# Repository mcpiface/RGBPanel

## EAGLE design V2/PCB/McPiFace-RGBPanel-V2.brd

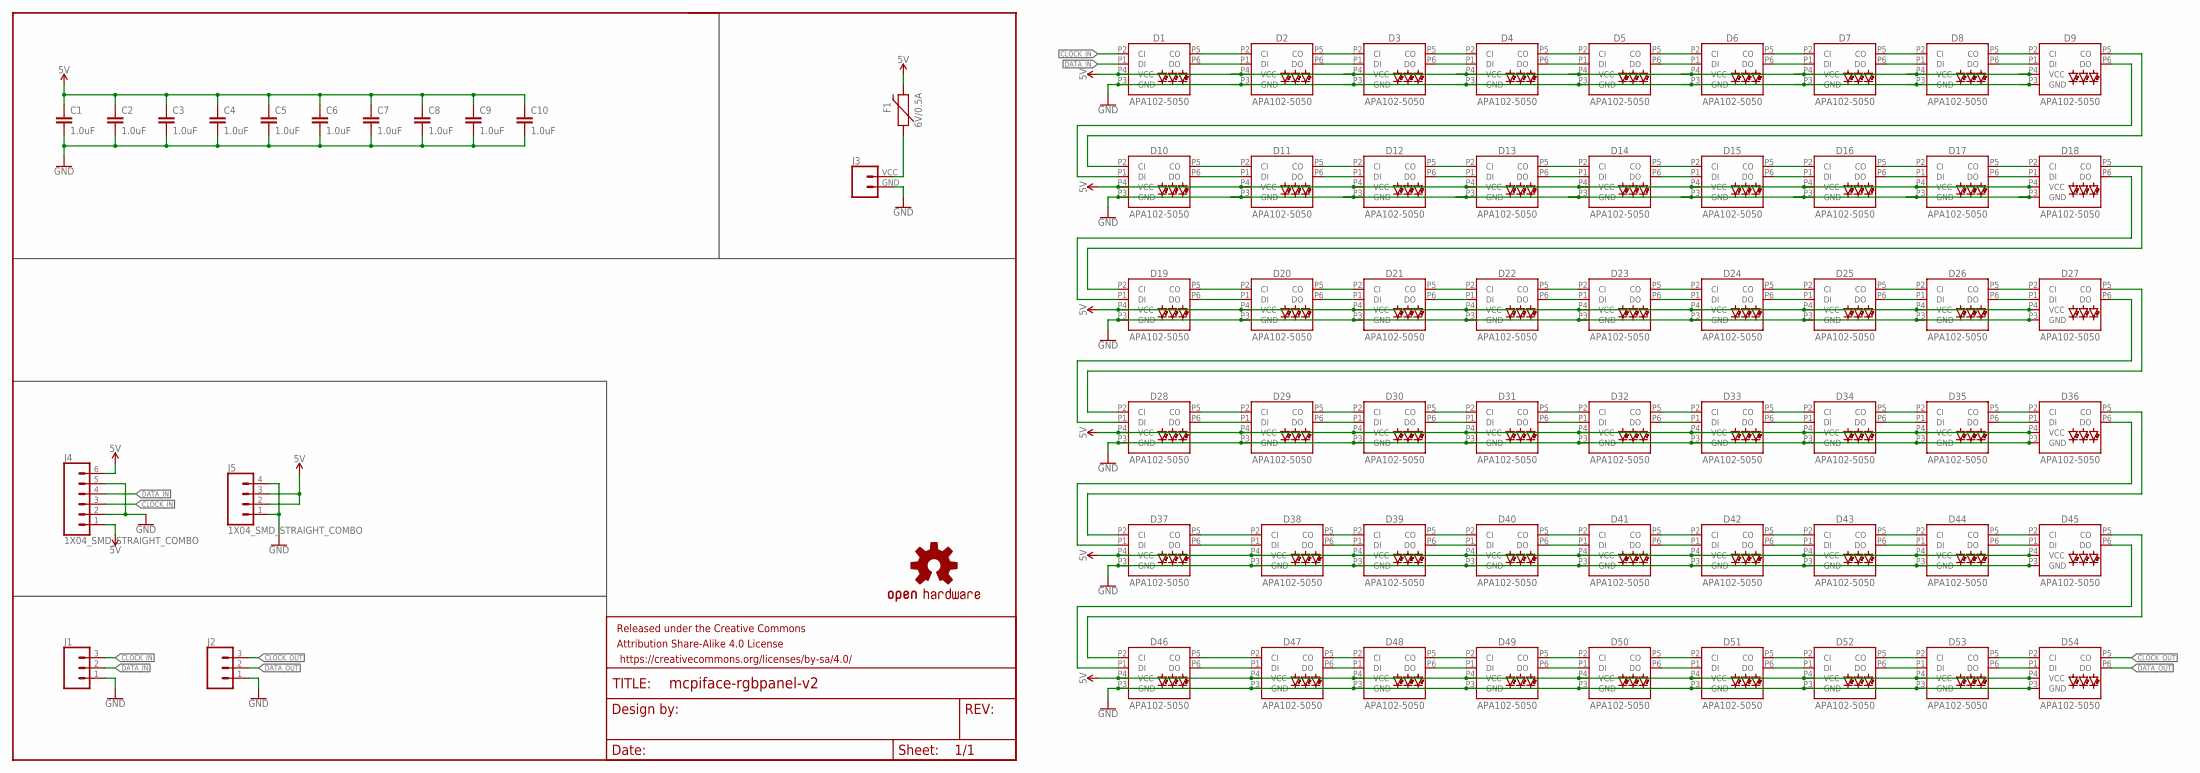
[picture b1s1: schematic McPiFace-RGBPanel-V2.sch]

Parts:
C1, C2, C3, C4, C5, C6, C7, C8, C9, C10: 1.0uF; 0805-CAP
D1, D2, D3, D4, D5, D6, D7, D8, D9, D10, D11, D12, D13, D14, D15, D16, D17, D18, D19, D20, D21, D22, D23, D24, D25, D26, D27, D28, D29, D30, D31, D32, D33, D34, D35, D36, D37, D38, D39, D40, D41, D42, D43, D44, D45, D46, D47, D48, D49, D50, D51, D52, D53, D54: APA102-5050
F1: 6V/0.5A; 1206
FRAME1: FRAME-LETTER; CREATIVE_COMMONS
J1, J2: CONN_03SMD; 1X03-1MM-RA
J3: CONN_02JST-2-PH-VERT; JST-2-SMD-VERT
J4: 1X04_SMD_STRAIGHT_COMBO; 1X06_SMD_STRAIGHT_COMBO
J5: 1X04_SMD_STRAIGHT_COMBO; 1X04_SMD_VERTICAL_COMBO
LOGO1: OSHW-LOGOL; OSHW-LOGO-L

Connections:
5V: C1.1, C2.1, C3.1, C4.1, C5.1, C6.1, C7.1, C8.1, C9.1, C10.1, D1.P4 (VCC), D2.P4 (VCC), D3.P4 (VCC), D4.P4 (VCC), D5.P4 (VCC), D6.P4 (VCC), D7.P4 (VCC), D8.P4 (VCC), D9.P4 (VCC), D10.P4 (VCC), D11.P4 (VCC), D12.P4 (VCC), D13.P4 (VCC), D14.P4 (VCC), D15.P4 (VCC), D16.P4 (VCC), D17.P4 (VCC), D18.P4 (VCC), D19.P4 (VCC), D20.P4 (VCC), D21.P4 (VCC), D22.P4 (VCC), D23.P4 (VCC), D24.P4 (VCC), D25.P4 (VCC), D26.P4 (VCC), D27.P4 (VCC), D28.P4 (VCC), D29.P4 (VCC), D30.P4 (VCC), D31.P4 (VCC), D32.P4 (VCC), D33.P4 (VCC), D34.P4 (VCC), D35.P4 (VCC), D36.P4 (VCC), D37.P4 (VCC), D38.P4 (VCC), D39.P4 (VCC), D40.P4 (VCC), D41.P4 (VCC), D42.P4 (VCC), D43.P4 (VCC), D44.P4 (VCC), D45.P4 (VCC), D46.P4 (VCC), D47.P4 (VCC), D48.P4 (VCC), D49.P4 (VCC), D50.P4 (VCC), D51.P4 (VCC), D52.P4 (VCC), D53.P4 (VCC), D54.P4 (VCC), F1.2, J4.1, J4.6, J5.2, J5.3
CLOCK_IN: D1.P2 (CI), J1.3, J4.3
CLOCK_OUT: D54.P5 (CO), J2.3
DATA_IN: D1.P1 (DI), J1.2, J4.4
DATA_OUT: D54.P6 (DO), J2.2
GND: C1.2, C2.2, C3.2, C4.2, C5.2, C6.2, C7.2, C8.2, C9.2, C10.2, D1.P3 (GND), D2.P3 (GND), D3.P3 (GND), D4.P3 (GND), D5.P3 (GND), D6.P3 (GND), D7.P3 (GND), D8.P3 (GND), D9.P3 (GND), D10.P3 (GND), D11.P3 (GND), D12.P3 (GND), D13.P3 (GND), D14.P3 (GND), D15.P3 (GND), D16.P3 (GND), D17.P3 (GND), D18.P3 (GND), D19.P3 (GND), D20.P3 (GND), D21.P3 (GND), D22.P3 (GND), D23.P3 (GND), D24.P3 (GND), D25.P3 (GND), D26.P3 (GND), D27.P3 (GND), D28.P3 (GND), D29.P3 (GND), D30.P3 (GND), D31.P3 (GND), D32.P3 (GND), D33.P3 (GND), D34.P3 (GND), D35.P3 (GND), D36.P3 (GND), D37.P3 (GND), D38.P3 (GND), D39.P3 (GND), D40.P3 (GND), D41.P3 (GND), D42.P3 (GND), D43.P3 (GND), D44.P3 (GND), D45.P3 (GND), D46.P3 (GND), D47.P3 (GND), D48.P3 (GND), D49.P3 (GND), D50.P3 (GND), D51.P3 (GND), D52.P3 (GND), D53.P3 (GND), D54.P3 (GND), J1.1, J2.1, J3.GND (1), J4.2, J4.5, J5.1, J5.4
unnamed: D10.P5 (CO), D11.P2 (CI)
unnamed: D10.P6 (DO), D11.P1 (DI)
unnamed: D11.P5 (CO), D12.P2 (CI)
unnamed: D11.P6 (DO), D12.P1 (DI)
unnamed: F1.1, J3.VCC (2)
unnamed: D9.P5 (CO), D10.P2 (CI)
unnamed: D9.P6 (DO), D10.P1 (DI)
unnamed: D18.P6 (DO), D19.P1 (DI)
unnamed: D18.P5 (CO), D19.P2 (CI)
unnamed: D15.P5 (CO), D16.P2 (CI)
unnamed: D15.P6 (DO), D16.P1 (DI)
unnamed: D12.P5 (CO), D13.P2 (CI)
unnamed: D12.P6 (DO), D13.P1 (DI)
unnamed: D19.P6 (DO), D20.P1 (DI)
unnamed: D16.P5 (CO), D17.P2 (CI)
unnamed: D19.P5 (CO), D20.P2 (CI)
unnamed: D16.P6 (DO), D17.P1 (DI)
unnamed: D13.P5 (CO), D14.P2 (CI)
unnamed: D13.P6 (DO), D14.P1 (DI)
unnamed: D14.P6 (DO), D15.P1 (DI)
unnamed: D14.P5 (CO), D15.P2 (CI)
unnamed: D20.P6 (DO), D21.P1 (DI)
unnamed: D1.P5 (CO), D2.P2 (CI)
unnamed: D17.P5 (CO), D18.P2 (CI)
unnamed: D17.P6 (DO), D18.P1 (DI)
unnamed: D20.P5 (CO), D21.P2 (CI)
unnamed: D21.P6 (DO), D22.P1 (DI)
unnamed: D21.P5 (CO), D22.P2 (CI)
unnamed: D22.P6 (DO), D23.P1 (DI)
unnamed: D22.P5 (CO), D23.P2 (CI)
unnamed: D23.P6 (DO), D24.P1 (DI)
unnamed: D23.P5 (CO), D24.P2 (CI)
unnamed: D24.P6 (DO), D25.P1 (DI)
unnamed: D24.P5 (CO), D25.P2 (CI)
unnamed: D25.P6 (DO), D26.P1 (DI)
unnamed: D1.P6 (DO), D2.P1 (DI)
unnamed: D25.P5 (CO), D26.P2 (CI)
unnamed: D26.P6 (DO), D27.P1 (DI)
unnamed: D26.P5 (CO), D27.P2 (CI)
unnamed: D27.P5 (CO), D28.P2 (CI)
unnamed: D27.P6 (DO), D28.P1 (DI)
unnamed: D28.P6 (DO), D29.P1 (DI)
unnamed: D28.P5 (CO), D29.P2 (CI)
unnamed: D29.P6 (DO), D30.P1 (DI)
unnamed: D29.P5 (CO), D30.P2 (CI)
unnamed: D30.P6 (DO), D31.P1 (DI)
unnamed: D30.P5 (CO), D31.P2 (CI)
unnamed: D31.P6 (DO), D32.P1 (DI)
unnamed: D31.P5 (CO), D32.P2 (CI)
unnamed: D32.P6 (DO), D33.P1 (DI)
unnamed: D32.P5 (CO), D33.P2 (CI)
unnamed: D33.P6 (DO), D34.P1 (DI)
unnamed: D33.P5 (CO), D34.P2 (CI)
unnamed: D34.P6 (DO), D35.P1 (DI)
unnamed: D34.P5 (CO), D35.P2 (CI)
unnamed: D35.P6 (DO), D36.P1 (DI)
unnamed: D35.P5 (CO), D36.P2 (CI)
unnamed: D36.P5 (CO), D37.P2 (CI)
unnamed: D36.P6 (DO), D37.P1 (DI)
unnamed: D37.P6 (DO), D38.P1 (DI)
unnamed: D37.P5 (CO), D38.P2 (CI)
unnamed: D38.P6 (DO), D39.P1 (DI)
unnamed: D38.P5 (CO), D39.P2 (CI)
unnamed: D39.P6 (DO), D40.P1 (DI)
unnamed: D39.P5 (CO), D40.P2 (CI)
unnamed: D40.P6 (DO), D41.P1 (DI)
unnamed: D40.P5 (CO), D41.P2 (CI)
unnamed: D2.P5 (CO), D3.P2 (CI)
unnamed: D2.P6 (DO), D3.P1 (DI)
unnamed: D3.P5 (CO), D4.P2 (CI)
unnamed: D3.P6 (DO), D4.P1 (DI)
unnamed: D4.P5 (CO), D5.P2 (CI)
unnamed: D4.P6 (DO), D5.P1 (DI)
unnamed: D5.P5 (CO), D6.P2 (CI)
unnamed: D5.P6 (DO), D6.P1 (DI)
unnamed: D6.P5 (CO), D7.P2 (CI)
unnamed: D6.P6 (DO), D7.P1 (DI)
unnamed: D7.P5 (CO), D8.P2 (CI)
unnamed: D7.P6 (DO), D8.P1 (DI)
unnamed: D8.P5 (CO), D9.P2 (CI)
unnamed: D8.P6 (DO), D9.P1 (DI)
unnamed: D41.P6 (DO), D42.P1 (DI)
unnamed: D41.P5 (CO), D42.P2 (CI)
unnamed: D42.P6 (DO), D43.P1 (DI)
unnamed: D42.P5 (CO), D43.P2 (CI)
unnamed: D43.P6 (DO), D44.P1 (DI)
unnamed: D43.P5 (CO), D44.P2 (CI)
unnamed: D44.P6 (DO), D45.P1 (DI)
unnamed: D44.P5 (CO), D45.P2 (CI)
unnamed: D45.P6 (DO), D46.P1 (DI)
unnamed: D45.P5 (CO), D46.P2 (CI)
unnamed: D46.P6 (DO), D47.P1 (DI)
unnamed: D46.P5 (CO), D47.P2 (CI)
unnamed: D47.P6 (DO), D48.P1 (DI)
unnamed: D47.P5 (CO), D48.P2 (CI)
unnamed: D48.P6 (DO), D49.P1 (DI)
unnamed: D48.P5 (CO), D49.P2 (CI)
unnamed: D49.P6 (DO), D50.P1 (DI)
unnamed: D49.P5 (CO), D50.P2 (CI)
unnamed: D50.P6 (DO), D51.P1 (DI)
unnamed: D50.P5 (CO), D51.P2 (CI)
unnamed: D51.P6 (DO), D52.P1 (DI)
unnamed: D51.P5 (CO), D52.P2 (CI)
unnamed: D52.P6 (DO), D53.P1 (DI)
unnamed: D52.P5 (CO), D53.P2 (CI)
unnamed: D53.P6 (DO), D54.P1 (DI)
unnamed: D53.P5 (CO), D54.P2 (CI)

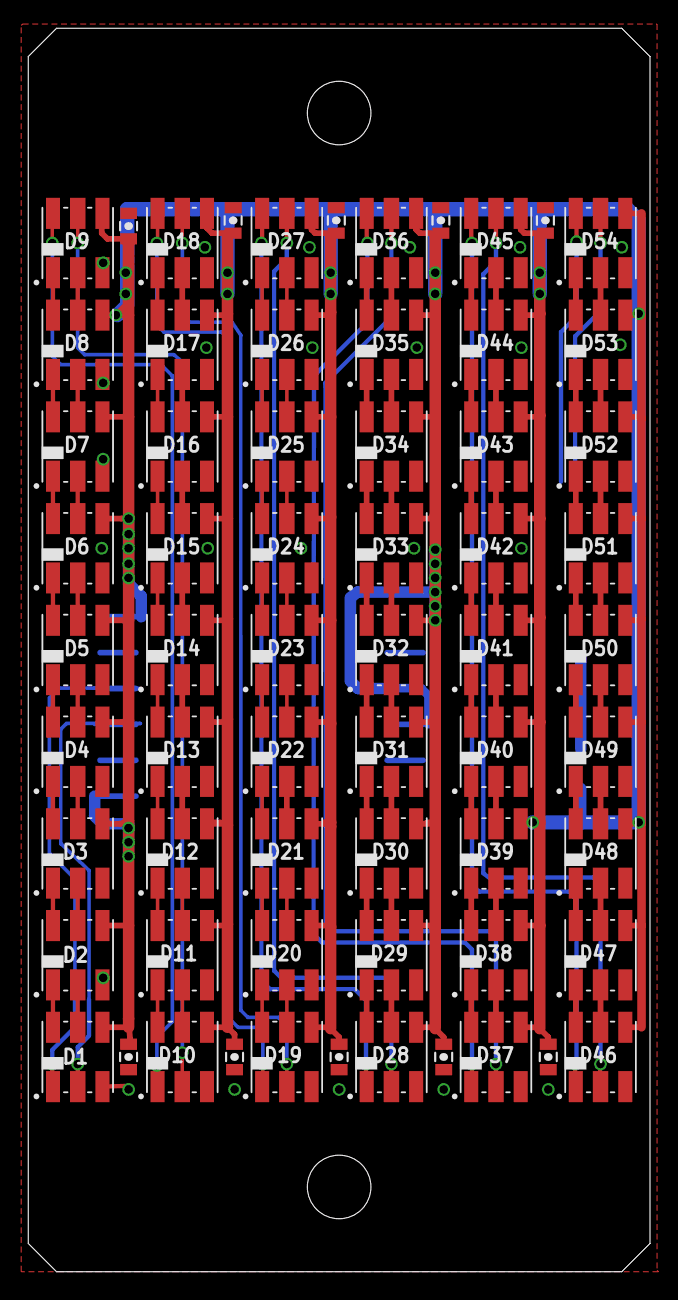
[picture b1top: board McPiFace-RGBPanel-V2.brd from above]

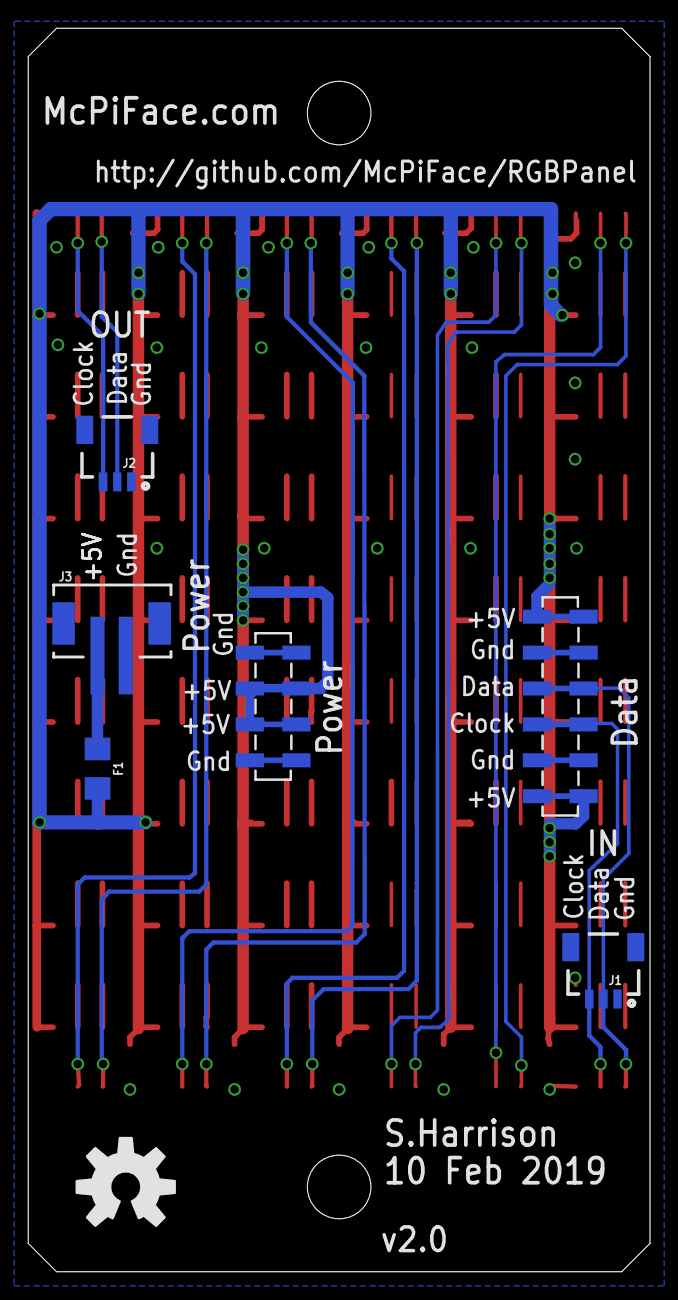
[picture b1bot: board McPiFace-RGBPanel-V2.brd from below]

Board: 2 copper layers, 44.0 x 88.0 mm, 72 parts (7 on the bottom side), 113 nets.

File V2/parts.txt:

Partlist

Exported from McPiFace-RGBPanel-V2.brd at 10/02/2019 03:54

EAGLE Version 7.4.0 Copyright (c) 1988-2015 CadSoft

Assembly variant: 

Part     Value                   Package                 Library             Position (mm)         Orientation

C1       1.0uF                   0805-CAP                SparkFun-Capacitors (29.4 15.2)           R270
C2       1.0uF                   0805-CAP                SparkFun-Capacitors (21.8 74.4)           R90
C3       1.0uF                   0805-CAP                SparkFun-Capacitors (29.2 74.4)           R90
C4       1.0uF                   0805-CAP                SparkFun-Capacitors (14.5 74.4)           R90
C5       1.0uF                   0805-CAP                SparkFun-Capacitors (14.6 15.2)           R270
C6       1.0uF                   0805-CAP                SparkFun-Capacitors (7.1 15.2)            R270
C7       1.0uF                   0805-CAP                SparkFun-Capacitors (22 15.2)             R270
C8       1.0uF                   0805-CAP                SparkFun-Capacitors (36.8 15.2)           R270
C9       1.0uF                   0805-CAP                SparkFun-Capacitors (7.1 74)              R90
C10      1.0uF                   0805-CAP                SparkFun-Capacitors (36.6 74.4)           R90
D1       APA102-5050             APA102-5050             SparkFun-LED        (3.5 15.2)            R0
D2       APA102-5050             APA102-5050             SparkFun-LED        (3.5 22.4)            R0
D3       APA102-5050             APA102-5050             SparkFun-LED        (3.5 29.6)            R0
D4       APA102-5050             APA102-5050             SparkFun-LED        (3.5 36.8)            R0
D5       APA102-5050             APA102-5050             SparkFun-LED        (3.5 44)              R0
D6       APA102-5050             APA102-5050             SparkFun-LED        (3.5 51.2)            R0
D7       APA102-5050             APA102-5050             SparkFun-LED        (3.5 58.4)            R0
D8       APA102-5050             APA102-5050             SparkFun-LED        (3.5 65.6)            R0
D9       APA102-5050             APA102-5050             SparkFun-LED        (3.5 72.8)            R0
D10      APA102-5050             APA102-5050             SparkFun-LED        (10.9 15.2)           R0
D11      APA102-5050             APA102-5050             SparkFun-LED        (10.9 22.4)           R0
D12      APA102-5050             APA102-5050             SparkFun-LED        (10.9 29.6)           R0
D13      APA102-5050             APA102-5050             SparkFun-LED        (10.9 36.8)           R0
D14      APA102-5050             APA102-5050             SparkFun-LED        (10.9 44)             R0
D15      APA102-5050             APA102-5050             SparkFun-LED        (10.9 51.2)           R0
D16      APA102-5050             APA102-5050             SparkFun-LED        (10.9 58.4)           R0
D17      APA102-5050             APA102-5050             SparkFun-LED        (10.9 65.6)           R0
D18      APA102-5050             APA102-5050             SparkFun-LED        (10.9 72.8)           R0
D19      APA102-5050             APA102-5050             SparkFun-LED        (18.3 15.2)           R0
D20      APA102-5050             APA102-5050             SparkFun-LED        (18.3 22.4)           R0
D21      APA102-5050             APA102-5050             SparkFun-LED        (18.3 29.6)           R0
D22      APA102-5050             APA102-5050             SparkFun-LED        (18.3 36.8)           R0
D23      APA102-5050             APA102-5050             SparkFun-LED        (18.3 44)             R0
D24      APA102-5050             APA102-5050             SparkFun-LED        (18.3 51.2)           R0
D25      APA102-5050             APA102-5050             SparkFun-LED        (18.3 58.4)           R0
D26      APA102-5050             APA102-5050             SparkFun-LED        (18.3 65.6)           R0
D27      APA102-5050             APA102-5050             SparkFun-LED        (18.3 72.8)           R0
D28      APA102-5050             APA102-5050             SparkFun-LED        (25.7 15.2)           R0
D29      APA102-5050             APA102-5050             SparkFun-LED        (25.7 22.4)           R0
D30      APA102-5050             APA102-5050             SparkFun-LED        (25.7 29.6)           R0
D31      APA102-5050             APA102-5050             SparkFun-LED        (25.7 36.8)           R0
D32      APA102-5050             APA102-5050             SparkFun-LED        (25.7 44)             R0
D33      APA102-5050             APA102-5050             SparkFun-LED        (25.7 51.2)           R0
D34      APA102-5050             APA102-5050             SparkFun-LED        (25.7 58.4)           R0
D35      APA102-5050             APA102-5050             SparkFun-LED        (25.7 65.6)           R0
D36      APA102-5050             APA102-5050             SparkFun-LED        (25.7 72.8)           R0
D37      APA102-5050             APA102-5050             SparkFun-LED        (33.1 15.2)           R0
D38      APA102-5050             APA102-5050             SparkFun-LED        (33.1 22.4)           R0
D39      APA102-5050             APA102-5050             SparkFun-LED        (33.1 29.6)           R0
D40      APA102-5050             APA102-5050             SparkFun-LED        (33.1 36.8)           R0
D41      APA102-5050             APA102-5050             SparkFun-LED        (33.1 44)             R0
D42      APA102-5050             APA102-5050             SparkFun-LED        (33.1 51.2)           R0
D43      APA102-5050             APA102-5050             SparkFun-LED        (33.1 58.4)           R0
D44      APA102-5050             APA102-5050             SparkFun-LED        (33.1 65.6)           R0
D45      APA102-5050             APA102-5050             SparkFun-LED        (33.1 72.8)           R0
D46      APA102-5050             APA102-5050             SparkFun-LED        (40.5 15.2)           R0
D47      APA102-5050             APA102-5050             SparkFun-LED        (40.5 22.4)           R0
D48      APA102-5050             APA102-5050             SparkFun-LED        (40.5 29.6)           R0
D49      APA102-5050             APA102-5050             SparkFun-LED        (40.5 36.8)           R0
D50      APA102-5050             APA102-5050             SparkFun-LED        (40.5 44)             R0
D51      APA102-5050             APA102-5050             SparkFun-LED        (40.5 51.2)           R0
D52      APA102-5050             APA102-5050             SparkFun-LED        (40.5 58.4)           R0
D53      APA102-5050             APA102-5050             SparkFun-LED        (40.5 65.6)           R0
D54      APA102-5050             APA102-5050             SparkFun-LED        (40.5 72.8)           R0
F1       6V/0.5A                 1206                    SparkFun-Fuses      (39.1 35.6)           MR270
J1                               1X03-1MM-RA             SparkFun-Connectors (3.3 19.3)            MR180
J2                               1X03-1MM-RA             SparkFun-Connectors (37.7 55.9)           MR180
J3                               JST-2-SMD-VERT          ThingySticks        (38.1 45.6)           MR0
J4       1X04_SMD_STRAIGHT_COMBO 1X06_SMD_STRAIGHT_COMBO SparkFun-Connectors (6.35 33.655)         MR90
J5       1X04_SMD_STRAIGHT_COMBO 1X04_SMD_VERTICAL_COMBO SparkFun-Connectors (26.67 36.195)        MR90

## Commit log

2019-02-10 Added V1 from ThingySticks repository.
    Note: This has routing issues (overlaps). Do not use!
2019-02-10 V2 - using APA102's for bettwe communications when using a Raspberry Pi
2019-02-10 Added readme

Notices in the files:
parts and their libraries:
SparkFun-Aesthetics: Licensing: Creative Commons ShareAlike 4.0 International - https://creativecommons.org/licenses/by-sa/4.0
SparkFun-Aesthetics: Released under the Creative Commons Attribution Share-Alike 4.0 License
SparkFun-Aesthetics: https://creativecommons.org/licenses/by-sa/4.0
